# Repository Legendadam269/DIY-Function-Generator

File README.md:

# DIY-Function-Generator
This project is a function generator system built using an AD9833 programmable waveform generator, an Arduino Nano, and a TL071 op-amp output stage.
The system generates sine, square, and triangle waveforms with adjustable frequency. A
rotary encoder is used for user input, allowing the frequency and waveform type to be modified
in real time. A 16×2 I2C LCD display shows the selected waveform and current frequency.
The circuit includes a dual ±12V power supply and a regulated +5V output using LM7812,
LM7912, and LM7805 regulators to power the op-amp, Arduino, and display. The TL071
op-amp amplifies and conditions the AD9833 output before it is sent to a BNC connector for
external use.
Overall, this design produces a compact, user-controlled digital function generator suitable for
lab use, testing circuits, and signal analysis.

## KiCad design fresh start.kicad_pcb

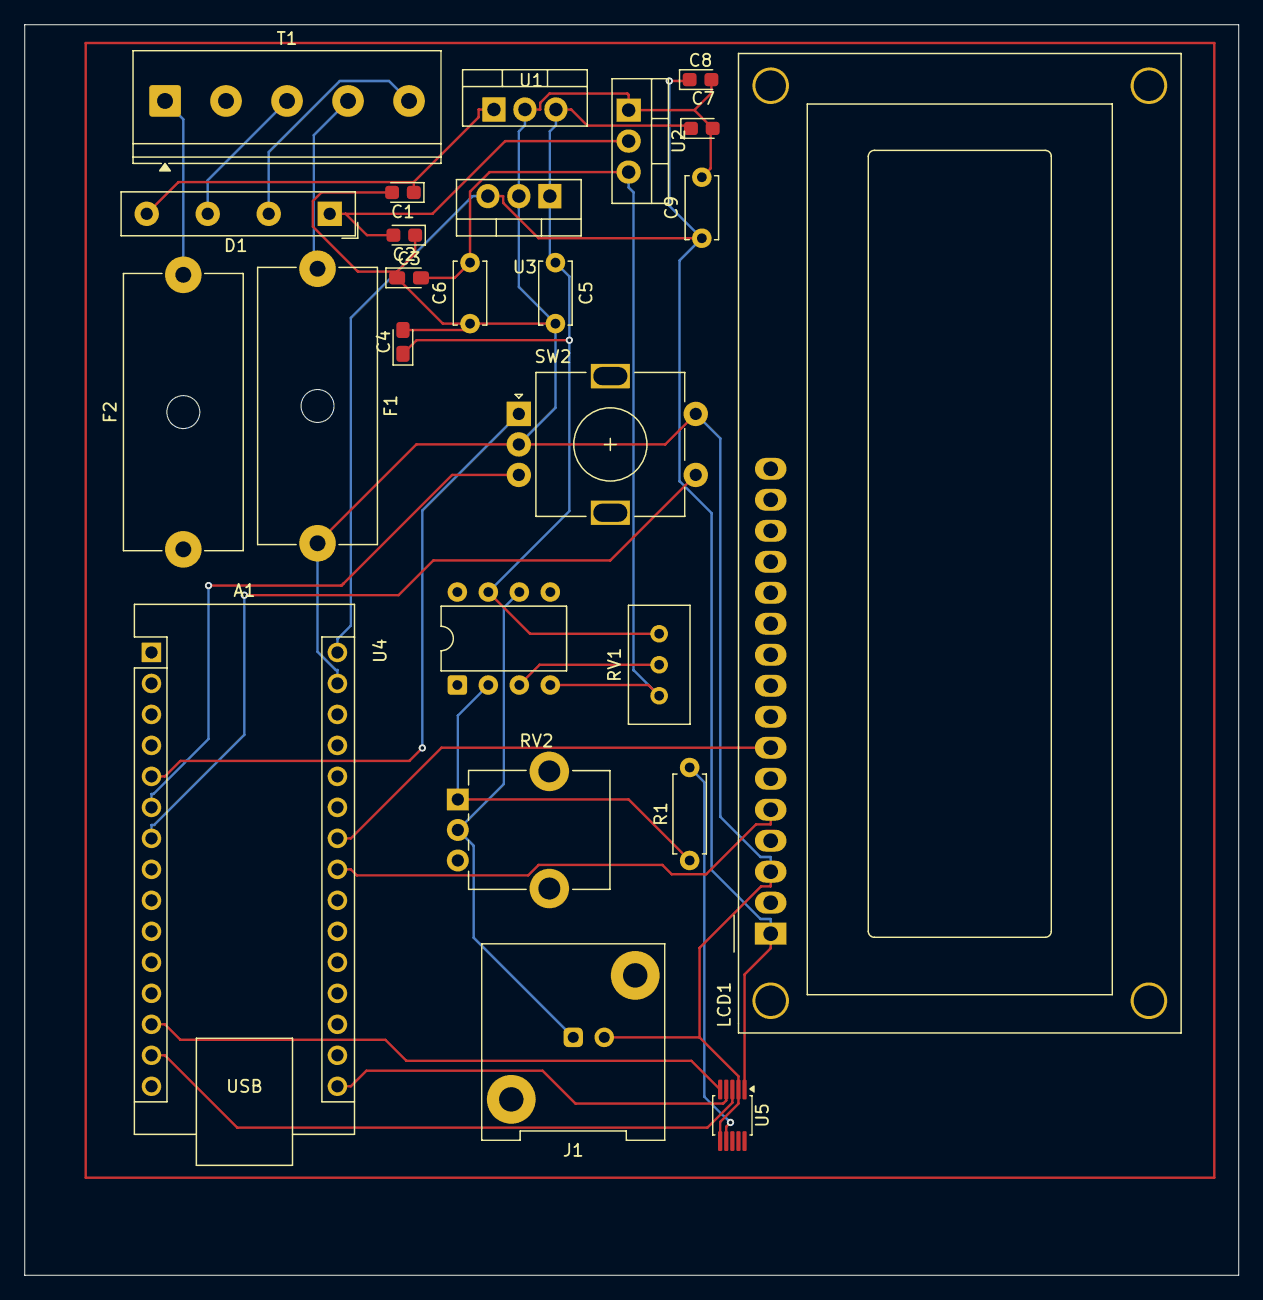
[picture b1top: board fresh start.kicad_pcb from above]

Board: 2 copper layers, 99.5 x 102.5 mm, 25 parts (0 on the bottom side), 22 nets.

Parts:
A1: Arduino_Nano_v3.x; Arduino_Nano
C1, C2: 1000u; CP_EIA-2012-15_AVX-P
C3, C4: 1000u; CP_EIA-2012-12_Kemet-R_HandSolder
C5, C6, C9: 100nf; C_Disc_D5.0mm_W2.5mm_P5.00mm
C7, C8: 10u; CP_EIA-2012-15_AVX-P
D1: B40C2300-1500A; Diode_Bridge_19.0x3.5x10.0mm_P5.0mm
F1: 2A; Fuseholder_Cylinder-5x20mm_Schurter_0031_8201_Horizontal_Op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
F2: FUSE; Fuseholder_Cylinder-5x20mm_Schurter_0031_8201_Horizontal_Op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
J1: Conn_Coaxial; BNC_Amphenol_031-5539_Vertical
LCD1: WC1602A
R1: 2.2k; R_Axial_DIN0207_L6.3mm_D2.5mm_P7.62mm_Horizontal
RV1: 10k; Potentiometer_Bourns_3296W_Vertical
RV2: 50k; Potentiometer_Alpha_RD901F-40-00D_Single_Vertical_CircularH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
SW2: RotaryEncoder_Switch; RotaryEncoder_Alps_EC11E-Switch_Vertical_H20mm
T1: Transformer_1P_SS; TerminalBlock_Phoenix_PT-1,5-5-5.0-H_1x05_P5.00mm_Horizontal
U1: LM7812_TO220; TO-220-3_Vertical
U2: LM7912_TO220; TO-220-3_Vertical
U3: LM7805_TO220; TO-220-3_Vertical
U4: TL071; DIP-8_W7.62mm
U5: MSOP-10_3x3mm_P0.5mm

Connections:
+5V: A1.30 (VIN), C8.1, C9.1, LCD1.1 (+5V), U3.3 (VO), U5.1 (VCC)
+12V: C4.1, C5.1, C7.1, RV1.1, U1.3 (VO), U3.1 (VI), U4.7 (V+)
-12V: C3.2, C6.2, RV1.3, U2.3 (VO), U4.4 (V-)
GND: A1.29 (GND), C1.2, C2.1, C3.1, C4.2, C5.2, C6.1, C7.2, C8.2, C9.2, F1.2, J1.2 (Ext), LCD1.3 (GND), SW2.C, SW2.S2, U1.2 (GND), U2.1 (GND), U3.2 (GND), U5.2 (DGND), U5.6 (AGND)
unnamed: A1.23 (A4), LCD1.5 (SDA)
unnamed: A1.24 (A5), LCD1.7 (SCL)
unnamed: A1.5 (D2), SW2.A
unnamed: A1.6 (D3), SW2.B
unnamed: A1.7 (D4), SW2.S1
unnamed: A1.13 (D10), U5.5 (FSYNC)
unnamed: A1.14 (D11), U5.3 (SDATA)
unnamed: A1.16 (D13), U5.4 (SCLK)
unnamed: C1.1, D1.4 (+), U1.1 (VI)
unnamed: C2.2, D1.1 (-), U2.2 (VI)
unnamed: J1.1 (In), RV2.2, U4.6
unnamed: F2.2, T1.1 (AA)
unnamed: D1.3, T1.3 (SA)
unnamed: D1.2, T1.5 (SB)
unnamed: F1.1, T1.4 (SC)
unnamed: RV1.2, U4.3 (+)
unnamed: R1.1, RV2.1, U4.2 (-)
unnamed: R1.2, U5.7 (OUT)
